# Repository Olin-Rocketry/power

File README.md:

# Power

## Current Design 
**Two independent groups of 3 cells in series.** <br>
**Nominal voltage: 12.3V**  <br>
**Nominal current: 4000 mAh** <br>

### The 25R 18650 Li-ion Battery
- Discharge rate: 2000 mA
- Range of voltage: 3.6V (EoD) - 4.1V (EoC)
- Current rating: 2500mAh
- Max voltage (switch from CV to CC):  4.1V
- Icc (charging current) = .25 A 
- Max cycle life: 100 cycles  
- Normal capacity: 80% (assumed) 
- Temperature range: -20 - 50 C

## System Diagram 

## Power Distribution

## Rev1 Schematic *1/2021

## Rev1 PCB Layout and 3D Model *1/2021

### Subsystem loads 
| Subsystem | Voltage | Current |
|-----------|---------|---------|
| Solenoid  |  12.3V  |  880mA  |
|    GPS    |  3.3V   |  30mA   |  
|   Radio   |  3.3V   |  50mA *at 13dBm* |
| Flight Computer | 3.3V | |
| BMS | 5V | |

(Live Power Budget Sheet)[https://docs.google.com/spreadsheets/d/1nH3F-o1HZTds1WetEKFTd1lCUxuCh-wOJmA-jhke28s/edit?usp=sharing]

## Firmware 
### MVP
- Read temperature from thermistors 
- Read voltage level of each battery 
- Calculate current flowing out of each battery 

### Goal 
- Trigger safety break of line when temperature rating or voltage level is above threshold 
- Balance cells using voltage readings 
- Display voltage levels 
- Send data via MQTT (or save data to SD)

## Requirements 
[General Rules and Reqs 2019](http://www.soundingrocket.org/uploads/9/0/6/4/9064598/sa_cup_irec_rules___requirements_document_20191118__rev_d_final_.pdf)
[Design, Test, Eval Guide 2019](http://www.soundingrocket.org/uploads/9/0/6/4/9064598/sa_cup_irec-design_test___evaluation_guide_20191118__rev_c_final_.pdf)
 
| Req. ID   | Requirement | Implementation | Type |
|-----------|-------------|----------------|------|
|BAT_REQ_04 | Battery Life | The batteries shall provide at least 2500 mAh of charge to the non-COTS computer power flow | Team |
|BAT_REQ_05 | Battery Quantity | The battery management board shall manage two separate batteries | Team |
|BAT_REQ_06	| Battery Draw | The battery management board shall be able to supply an expected maximum of 2000 mA | Team |
|BAT_REQ_07	| Maximum Power | Draw	The battery management board shall not draw more than 250 mA during the mission| Team|
|BAT_REQ_08	| Overall Power | Draw	The battery management board shall not draw more than 100 mAh over the course of the mission |Team|

## Design Reviews 

[Design Review 1](https://docs.google.com/presentation/d/1L4w887s7x08WpU703jKznQMGognrjYOtB8_F7KaSsSU/edit?usp=sharing): Initial design validation for cell balancing, charging, and discharging *12/2019

[Design Review 2](https://docs.google.com/presentation/d/1s-o9i7a22b9S89c6PrSgXXXy9AWuLc9d6yVl3I3lAEo/edit#slide=id.gacddbe3730_0_0): Process design review touching on integration of ATMEGA, safety switches, and voltage distribution/regulation *12/2020

## Rev 2 Plans 
- USB input 
- Power supply input 
- Lin Reg for power input 
- 10k pull up resistor on RESET of Atmega16 
- Switch to non-smd or ATMEGA328
- Voltage difference monitored instead of direct analog to avoid 5.5V maximum

## Ordering PCBs From JLCPCB

For ordering the boards, go to JLCPCB.com, and click on "Quote Now" button.

JLCPCB (ShenzhenJLC Electronics Co., Ltd.), is the largest PCB prototype enterprise in China, and a high-tech manufacturer specializing in quick PCB prototype and small-batch PCB production. You can order a minimum of 5 PCBs for just $2.

First: Upload the gerber files for the board by clicking the "Add gerber file" button. You’ll notice a message at the bottom if the file is successfully uploaded.

A correctly uploaded gerber folder renders the board as follows:

Second: In order to get the board assembled (optional, based on the project requirements), select the "SMT Assembly option. It is important to select the side of the PCB that needs to be assembled, as well as the quantity for SMT. Press the "Confirm" button, then press the "Next" button.

Third: upload the BOM (Bill of Material) and CPL (Component Placement List) files and click the "Next" button. It is necessary to make sure that each of these files follow the jlcpcb specified BOM and CPL formats, respectively:
* [Sample BOM](https://jlcpcb.com//video/JLCSMT_Sample_BOM1.xlsx?_ga=2.42560357.1905056644.1612161700-100444678.1610257845)
* [Sample CPL](https://jlcpcb.com//video/JLCSMT_Sample_CPL1.xlsx?_ga=2.42560357.1905056644.1612161700-100444678.1610257845)
* [SMT FAQ's](https://support.jlcpcb.com/category/78-smt-assembly?_ga=2.42560357.1905056644.1612161700-100444678.1610257845)

Note: If there is an issue with the BOM/CPL formatting, the the page will keep erroring out until it is resolved.

Fourth: The parts are automatically detected through the uploaded BOM. They are also matched against jlcpcb's in-stock parts. It is important to go through each row and confirm if the auto-detected parts are the desired parts. Some parts will remain undetected if they cannot be assembled through SMT and require manual assembly post-deilvery.

Fifth: The website renders an assembled board using the CPL file. This feature can be used to review the placement of the components (including orientation). Once carefull reviewed, the next step is to download a list of parts remaining to be assembled towards the bottom of this page view. It is important to place an order for the remaining components to be manually assembled upon delivery. 

Sixth: Click on the “Save to Cart” button. Then, click on the "Secure Checkout" button. 

Last: Add the payment details and choose the suitable delivery method (this includes FedEx, DHL, and standard mail options). Then, place the order.

Optional: To review the production status of the board, click on the "Order History" button under username. Then, click on In Production > view progress to obtain timestamps for each of the production steps in real time. 

## Questions and Considerations

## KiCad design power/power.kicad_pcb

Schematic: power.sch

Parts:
BLED1: LED_0805; LED_0805_OEM; MPN 475-1410-1-ND
C1: 0.1uF; C_0805_2012Metric_Pad1.15x1.40mm_HandSolder
C2, C3, C4: 1uF; C_0805_2012Metric_Pad1.15x1.40mm_HandSolder
D1, D2: D_Shockley; SD103AW-13-F
D3: D_Zener_13V; D_13V_Zener; MPN 1SMB5928BT3GOSCT-ND
D4: LED_0805_Red; LED_0805_OEM; MPN 475-1415-1-ND
D5: LED_0805_Amber; LED_0805_OEM; MPN L71517CT-ND
FlySol1, FlySol2: SS110LW; D_SOD-123W_OEM; MPN SS110LWRVGCT-ND
HFLED1: LED_0805; LED_0805_OEM; MPN 475-1410-1-ND
HFuse1: 01530008Z; MPN 01530008Z
J1, J3, J4, J6, J7, J8: Conn_01x02_Female; nickle_pads_1x2
J2: Barrel_jack; barrel_jack_PJ-037A; MPN CP-037A-ND
J5: CONN_02X03; Pin_Header_Straight_2x03; MPN 609-3234-ND
J9: MM_F_RA_08; micromatch_female_ra_8; MPN 338070-8
J15: Conn_01x03_Male; PinHeader_1x03_P2.54mm_Vertical
Q1, Q2, Q3, Q4, Q5, Q6: BS170; TO-92_Inline
R1, R2, R3, R7, R8, R9: 100; R_0805_2012Metric_Pad1.15x1.40mm_HandSolder
R4, R5, R6, R10, R11, R12: 1.5K; R_0805_2012Metric_Pad1.15x1.40mm_HandSolder
R13: 133; R_0805_2012Metric_Pad1.15x1.40mm_HandSolder
R14: 20; R_0805_2012Metric_Pad1.15x1.40mm_HandSolder
R15: 115K; R_0805_2012Metric_Pad1.15x1.40mm_HandSolder
R16, R17, R20, R21: R_499; R_0805_OEM; MPN P499CCT-ND
R18, R19: R_1K; R_0805_OEM; MPN RNCP0805FTD1K00CT-ND
TH1, TH2, TH3, TH4, TH5, TH6: Thermistor
U1: ATMEGA16M1; TQFP-32_7x7mm_Pitch0.8mm; MPN ATMEGA16M1-AU-ND
U2: TPS2592xx; VSON-10-1EP_3x3mm_P0.5mm_EP1.65x2.4mm_ThermalVias
U3: LP5907MFX-3_3_NOPB; SOT-753; MPN LP5907MFX-3.3/NOPB; Digi-Key_PN 296-38557-1-ND
sol1, sol2: OSTTC03; OSTTC030162; MPN OSTTC030162
tres1sol1, tres1sol2: NMOS_CDS16; TRANS_CSD17312Q5; MPN CSD16322Q5

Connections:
+3V3: C4.2, J5.2, J9.1, J9.2, J9.3, J9.4, J9.5, J9.6, J9.7, R21.1, U1.4, U1.19, U1.21, U3.5
+12V: C2.1, C3.2, HFuse1.2, R16.1, U3.1
/12V_Burn_Wire: FlySol2.1 (K), sol2.1, tres1sol2.1 (S), tres1sol2.2 (S), tres1sol2.3 (S)
/12V_Solenoid: FlySol1.1 (K), sol1.1, tres1sol1.1 (S), tres1sol1.2 (S), tres1sol1.3 (S)
/12V_Switch: HFuse1.1, R17.1, tres1sol1.5 (D), tres1sol1.6 (D), tres1sol1.7 (D), tres1sol1.8 (D), tres1sol2.5 (D), tres1sol2.6 (D), tres1sol2.7 (D), tres1sol2.8 (D)
/B1A+: D1.1 (K), D2.2 (A), J1.1, Q1.1 (D), TH1.1
/B1A-: J1.2, J3.1, R1.2, TH2.1
/B1B+: C1.1, D2.1 (K), D3.1, J6.1, Q4.1 (D), R13.1, TH4.1, U2.3 (VIN), U2.4 (VIN), U2.5 (VIN)
/B1B-: J6.2, J7.1, R7.2, TH5.1
/B2A-: J3.2, J4.1, R2.2, TH3.1
/B2B-: J7.2, J8.1, R8.2, TH6.1
/BAT+: D1.2 (A), J2.1, R20.1
/EN_LDO: U1.15, U3.3
/FET1A: Q1.2 (G), U1.1
/FET1B: Q4.2 (G), U1.26
/FET2A: Q2.2 (G), U1.3
/FET2B: Q5.2 (G), U1.24
/FET3A: Q3.2 (G), U1.7
/FET3B: Q6.2 (G), U1.22
/MISO: J5.1, U1.8
/MOSI: J5.4, U1.9
/RESET: J5.5, U1.29, U1.31
/SCK: J5.3, U1.28
/V1A: R4.1, TH1.2, U1.32
/V1B: R10.1, TH4.2, U1.27
/V2A: R5.1, TH2.2, U1.2
/V2B: R11.1, TH5.2, U1.25
/V3A: R6.1, TH3.2, U1.6
/V3B: R12.1, TH6.2, U1.23
/burn-wire: J15.1, R19.1, tres1sol2.4 (G)
/solenoid: J15.2, R18.1, tres1sol1.4 (G)
GND: BLED1.1 (K), C1.2, C3.1, C4.1, D3.2, D4.1, D5.1, FlySol1.2 (A), FlySol2.2 (A), HFLED1.1 (K), J2.2, J4.2, J5.6, J8.2, J9.8, J15.3, R3.2, R4.2, R5.2, R6.2, R9.2, R10.2, R11.2, R12.2, R14.2, R15.2, R18.2, R19.2, U1.5, U1.20, U2.1 (dV/dT), U2.11 (GND), U3.2, sol1.2, sol1.3, sol2.2, sol2.3
unnamed: BLED1.2 (A), R16.2
unnamed: C2.2, U2.6 (OUT), U2.7 (OUT), U2.8 (OUT)
unnamed: D4.2, R20.2
unnamed: D5.2, R21.2
unnamed: HFLED1.2 (A), R17.2
unnamed: Q1.3 (S), Q2.1 (D), R1.1
unnamed: Q2.3 (S), Q3.1 (D), R2.1
unnamed: Q3.3 (S), R3.1
unnamed: Q4.3 (S), Q5.1 (D), R7.1
unnamed: Q5.3 (S), Q6.1 (D), R8.1
unnamed: Q6.3 (S), R9.1
unnamed: R13.2, R14.1, U2.2 (EN/UVLO)
unnamed: R15.1, U2.10 (ILIM)

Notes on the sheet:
Charge Shuttering
Programming Header
Battery Connectors
Power Flags
Thermal Monitoring
Microcontroller
Charging INPUT Connectors
1.5 W
Safety and Monitoring
Step Down Circuitry
To Teensy
12.3V 4A ----->
To Baro2
To Baro1
To IMU
To GPS
To Radio
Connections
4.1V
8.2V
12.3V
Voltage Monitoring
1K Ohms
LDO 12.3V -> 3.3V
Variable Output 12.3V
transistor
high-power fuse
trigger connectors
Recovery
Debugging LEDs
Power Output to Main Flight Computer

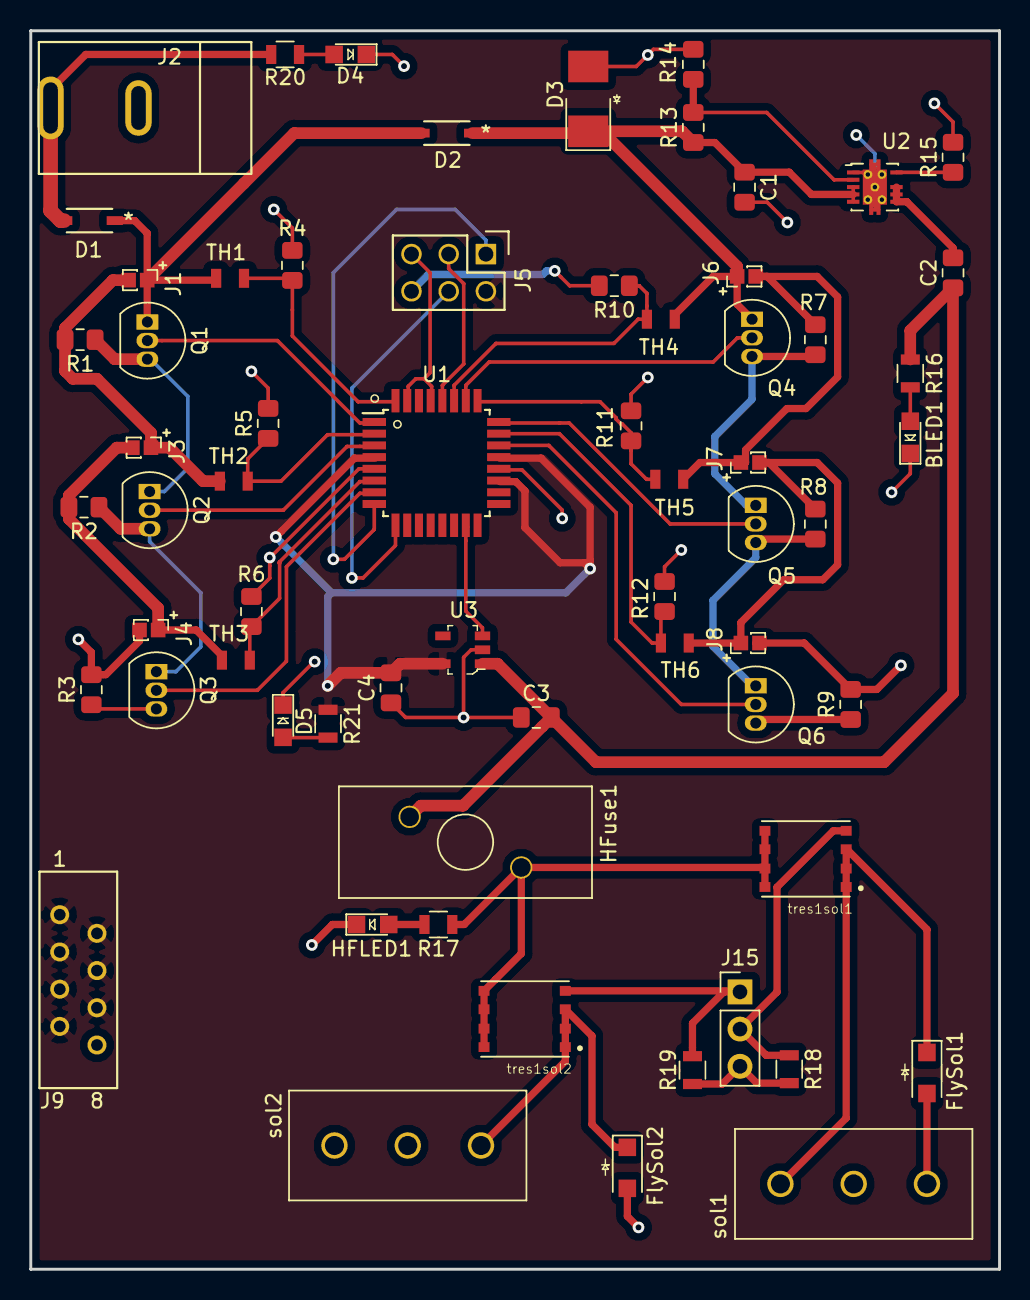
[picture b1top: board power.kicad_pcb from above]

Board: 2 copper layers, 66.1 x 84.5 mm, 64 parts (0 on the bottom side), 45 nets.

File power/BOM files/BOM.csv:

"Comment";"Designator";"Footprint";"LCSC Part #";"LCSC Part Type"
"NMOS_CDS16";"tres1sol1,tres1sol2";"TRANS_CSD17312Q5";"";""
"Conn_01x02_Female";"J6,J1,J3,J4,J7,J8";"nickle_pads_1x2";"";""
"1.5K";"R5,R6,R4,R12,R11,R10";"R_0805_2012Metric_Pad1.15x1.40mm_HandSolder";"";""
"R_499";"R20,R17,R16,R21";"R_0805_OEM";"";""
"R_1K";"R19,R18";"R_0805_OEM";"";""
"Conn_01x03_Male";"J15";"PinHeader_1x03_P2.54mm_Vertical";"";""
"CONN_02X03";"J5";"Pin_Header_Straight_2x03";"";""
"LP5907MFX-3_3_NOPB";"U3";"SOT-753";"";""
"BS170";"Q5,Q4,Q3,Q2,Q1,Q6";"TO-92_Inline";"";""
"ATMEGA16M1";"U1";"TQFP-32_7x7mm_Pitch0.8mm";"";""
"Thermistor";"TH4,TH6,TH5,TH3,TH2,TH1";"Thermistor";"";""
"115K";"R15";"R_0805_2012Metric_Pad1.15x1.40mm_HandSolder";"";""
"133";"R13";"R_0805_2012Metric_Pad1.15x1.40mm_HandSolder";"";""
"100";"R3,R2,R1,R9,R8,R7";"R_0805_2012Metric_Pad1.15x1.40mm_HandSolder";"";""
"01530008Z";"HFuse1";"01530008Z";"";""
"LED_0805";"HFLED1,BLED1";"LED_0805_OEM";"";""
"SS110LW";"FlySol2,FlySol1";"D_SOD-123W_OEM";"";""
"LED_0805_Amber";"D5";"LED_0805_OEM";"";""
"LED_0805_Red";"D4";"LED_0805_OEM";"";""
"1uF";"C4,C3,C2";"C_0805_2012Metric_Pad1.15x1.40mm_HandSolder";"";""
"D_Zener_13V";"D3";"D_13V_Zener";"";""
"Barrel_jack";"J2";"barrel_jack_PJ-037A";"";""
"D_Shockley";"D2,D1";"SD103AW-13-F";"";""
"20";"R14";"R_0805_2012Metric_Pad1.15x1.40mm_HandSolder";"";""
"0.1uF";"C1";"C_0805_2012Metric_Pad1.15x1.40mm_HandSolder";"";""
"OSTTC03";"sol1,sol2";"OSTTC030162";"";""
"MM_F_RA_08";"J9";"micromatch_female_ra_8";"";""
"TPS2592xx";"U2";"VSON-10-1EP_3x3mm_P0.5mm_EP1.65x2.4mm_ThermalVias";"";""

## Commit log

2020-10-02 Outline of power readme
2020-10-08 updated power specs
2020-10-08 linked DRs
2020-10-08 reqs docs and battery table
2020-10-30 Updated Schematic and System Diagram
2020-10-30 Complete system diagram
2020-11-20 changed MAX1468 datasheet
2020-11-21 power diagram
2020-11-23 added to sch
2020-11-23 added system diagram and power distribution
2020-11-23 Added proper power budgets
2020-11-23 changed to atmega16
2020-12-01 Proper atmega configuration with programming header pins
2020-12-05 negative terminals of bat
2020-12-08 wattage and values for charging circuit
2020-12-08 bleeding resistor values and wattage, discharging current sink circuit complete
2020-12-09 buck converters added and LDO added
2020-12-26 complete schematic
2020-12-28 rev 2 copy for bq76930 ic
2020-12-28 balancing with bq rev 2
2020-12-28 rev1 layout organization
2020-12-30 thermistor footprint
2020-12-31 removed extra thermistor
2021-01-01 separated charging from main board
2021-01-03 half layout
2021-01-03 complete layout
2021-01-05 power traces increased to 0.8
2021-01-05 generated bom and gerber files
2021-01-06 debugging LEDs, recovery
2021-01-07 layout complete other than missing recovery footprints
2021-01-11 final rev 1: nickel pads added and recovery footprint issues fixed
2021-01-12 ribbon added to sch and recovery wires increased and no connects added
2021-01-14 complete bms - 0 drc errors, ribbon cable, pads not on edge
2021-01-16 gerber folder
2021-01-16 cpl generation in /gerber
2021-01-16 BOM attempt 100000
2021-01-16 BOM generation attempt 10000001
2021-01-16 omggg
2021-01-16 new cpl
2021-01-16 if this doesn't work, jlcpcb can die
2021-01-16 Update CPL
2021-01-16 Add remaining parts list
2021-01-18 Add new gerbers
2021-01-19 complete bms with list checked
2021-01-22 final power
2021-01-22 complete jlc BOM and CPL and GERBER
2021-01-22 comma separation
2021-01-22 Fix U3 orientation
2021-01-27 screenshots of layout, sch, etc.
2021-01-27 screenshots
2021-01-28 updated purchasing links
2021-02-01 Add PCB order procedure
2021-02-01 Add JLCPCB order doc files
2021-04-13 Firmware goals
2021-04-16 charging
2021-04-17 added 10K on reset, power conditional setup for testing rev2

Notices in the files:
parts and their libraries:
Copyright 2016 Accelerated Designs. All rights reserved.
